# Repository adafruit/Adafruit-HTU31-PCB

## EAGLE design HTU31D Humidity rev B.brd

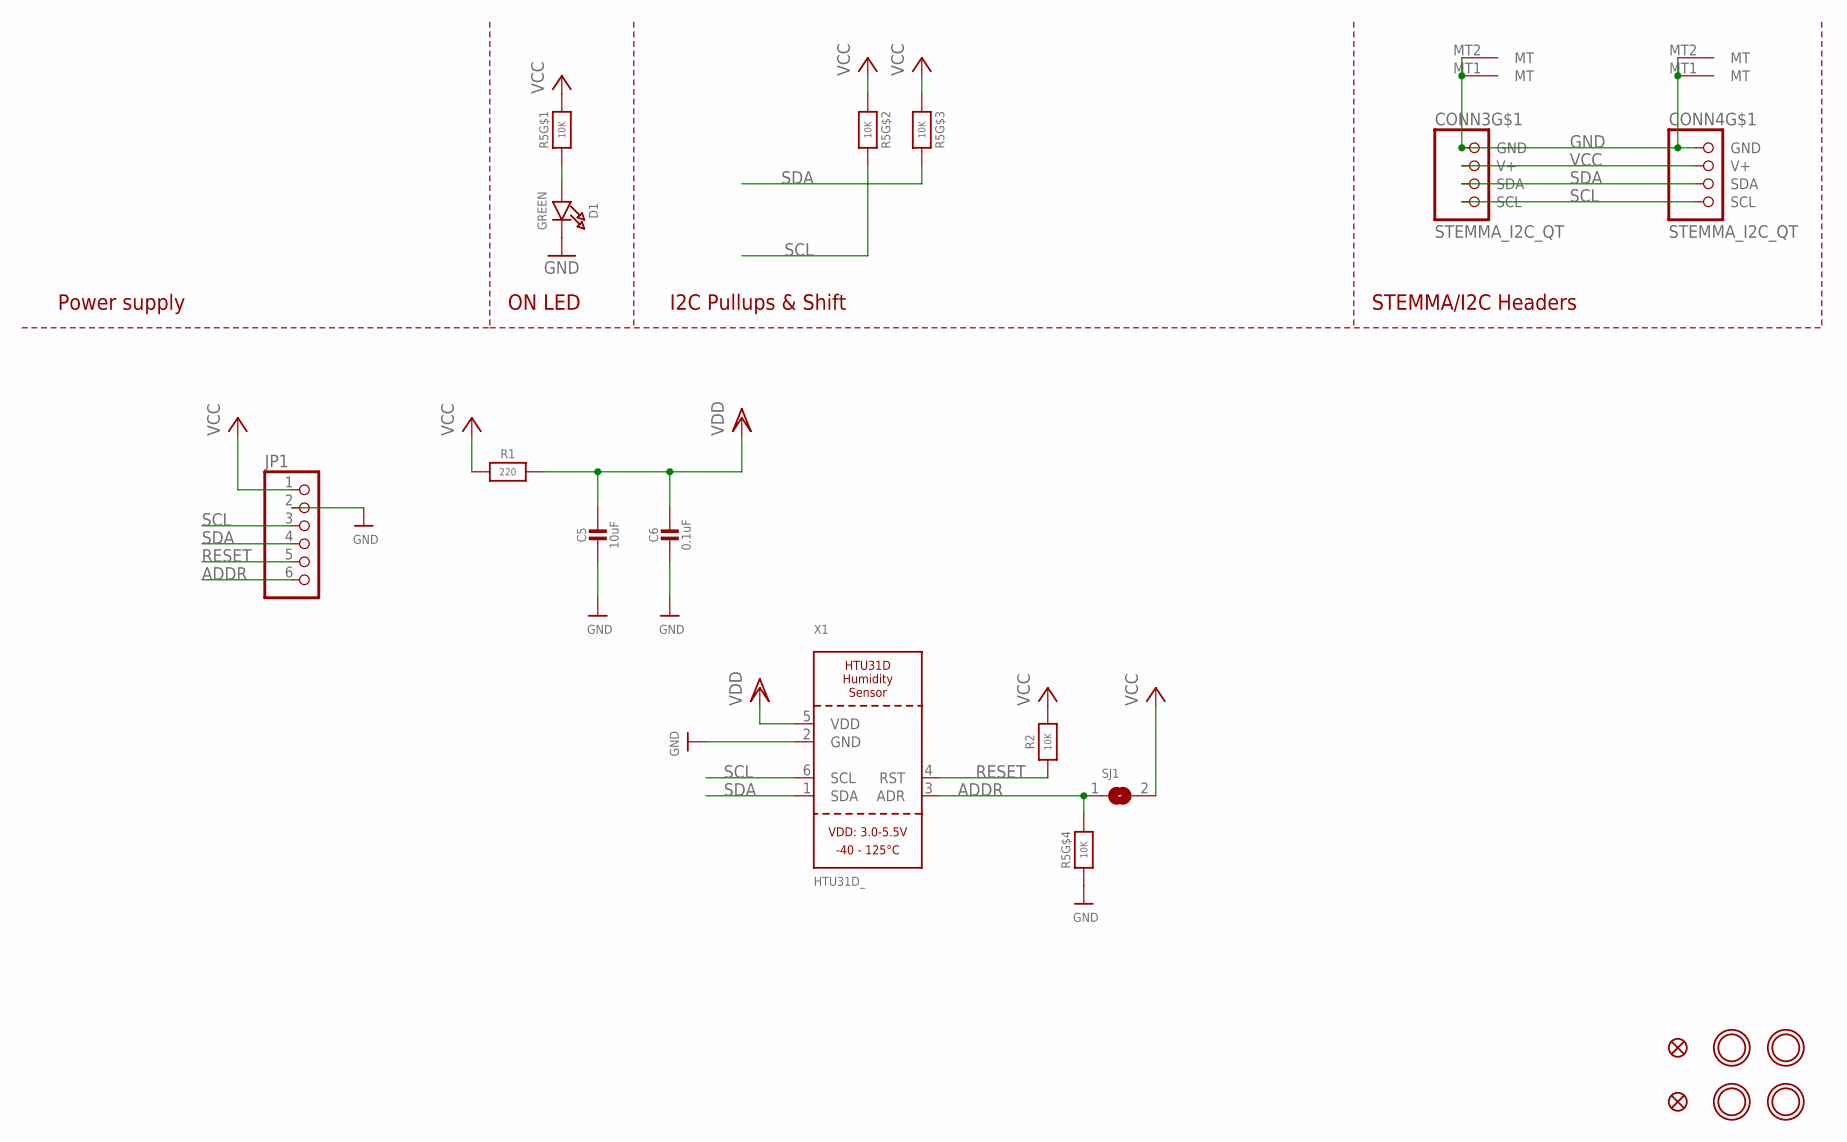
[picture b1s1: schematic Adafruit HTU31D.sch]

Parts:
C5: 10uF; 0805-NO
C6: 0.1uF; 0603-NO
CONN3, CONN4: STEMMA_I2C_QT; JST_SH4
D1: GREEN; CHIPLED_0603_NOOUTLINE
FID3, FID4: FIDUCIAL_1MM
JP1: HEADER-1X670MIL; 1X06_ROUND_70
R1: 220; 0603-NO
R2: 10K; 0603-NO
R5: 10K; RESPACK_4X0603
SJ1: SOLDERJUMPER; SOLDERJUMPER_ARROW_NOPASTE
U$19, U$20, U$22, U$25: MOUNTINGHOLE2.5; MOUNTINGHOLE_2.5_PLATED
X1: HTU31D_; HTU31D

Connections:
ADDR: JP1.6, R5.5 (2), SJ1.1, X1.3 (ADR)
GND: C5.2, C6.2, CONN3.1 (GND), CONN3.MT1 (MT), CONN3.MT2 (MT), CONN4.1 (GND), CONN4.MT1 (MT), CONN4.MT2 (MT), D1.C, JP1.2, R5.4 (1), X1.2 (GND)
unnamed: D1.A, R5.1
RESET: JP1.5, R2.1, X1.4 (RST)
SCL: CONN3.4 (SCL), CONN4.4 (SCL), JP1.3, R5.7 (2), X1.6 (SCL)
SDA: CONN3.3 (SDA), CONN4.3 (SDA), JP1.4, R5.6 (2), X1.1 (SDA)
VCC: CONN3.2 (V+), CONN4.2 (V+), JP1.1, R1.1, R2.2, R5.2 (1), R5.3 (1), R5.8 (2), SJ1.2
VDD: C5.1, C6.1, R1.2, X1.5 (VDD)

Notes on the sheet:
I2C Pullups & Shift
STEMMA/I2C Headers
ON LED
Power supply

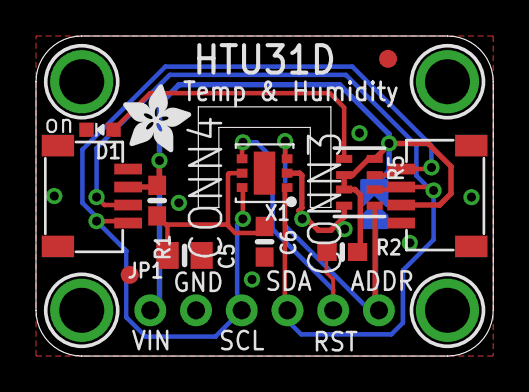
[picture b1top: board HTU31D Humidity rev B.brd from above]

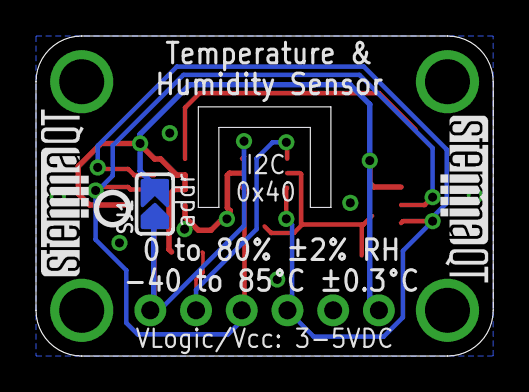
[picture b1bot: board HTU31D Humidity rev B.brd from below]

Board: 2 copper layers, 25.4 x 17.8 mm, 21 parts (4 on the bottom side), 8 nets.

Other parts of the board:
U$28: ADAFRUIT_3.5MM
U$29: PCBFEAT-REV-040
U$30, U$31: STEMMAQT

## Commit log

2021-08-11 Renamed pcb files

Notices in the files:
parts and their libraries:
microbuilder: This work is placed in the public domain, and may be freely used for commercial and non-commercial work with the following conditions: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
